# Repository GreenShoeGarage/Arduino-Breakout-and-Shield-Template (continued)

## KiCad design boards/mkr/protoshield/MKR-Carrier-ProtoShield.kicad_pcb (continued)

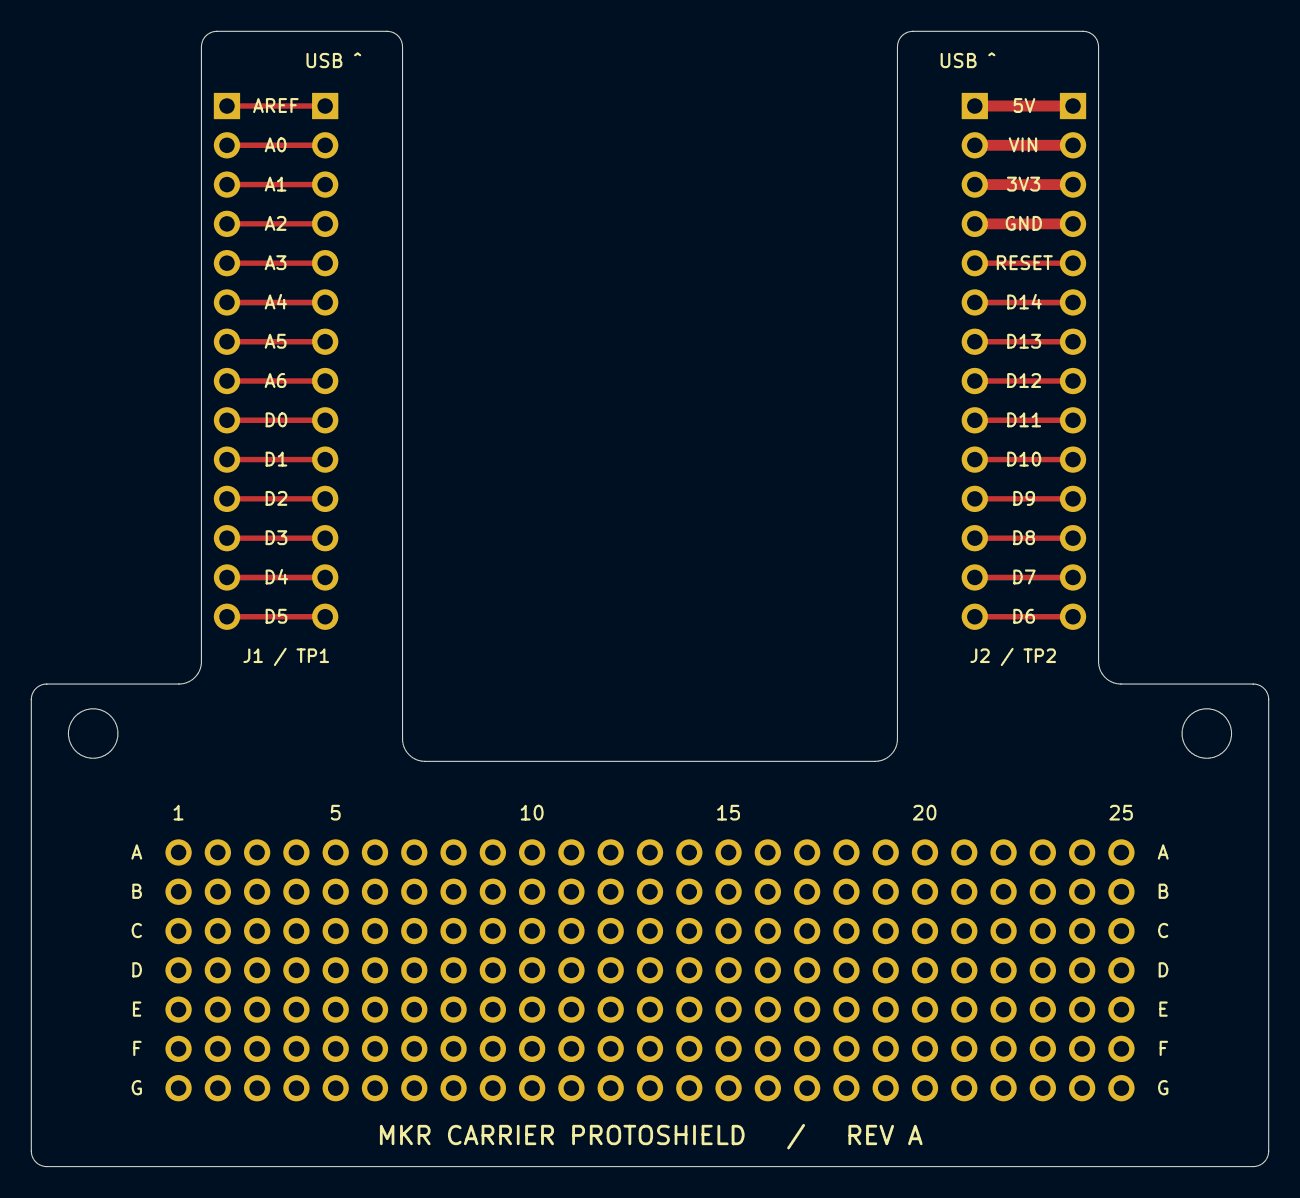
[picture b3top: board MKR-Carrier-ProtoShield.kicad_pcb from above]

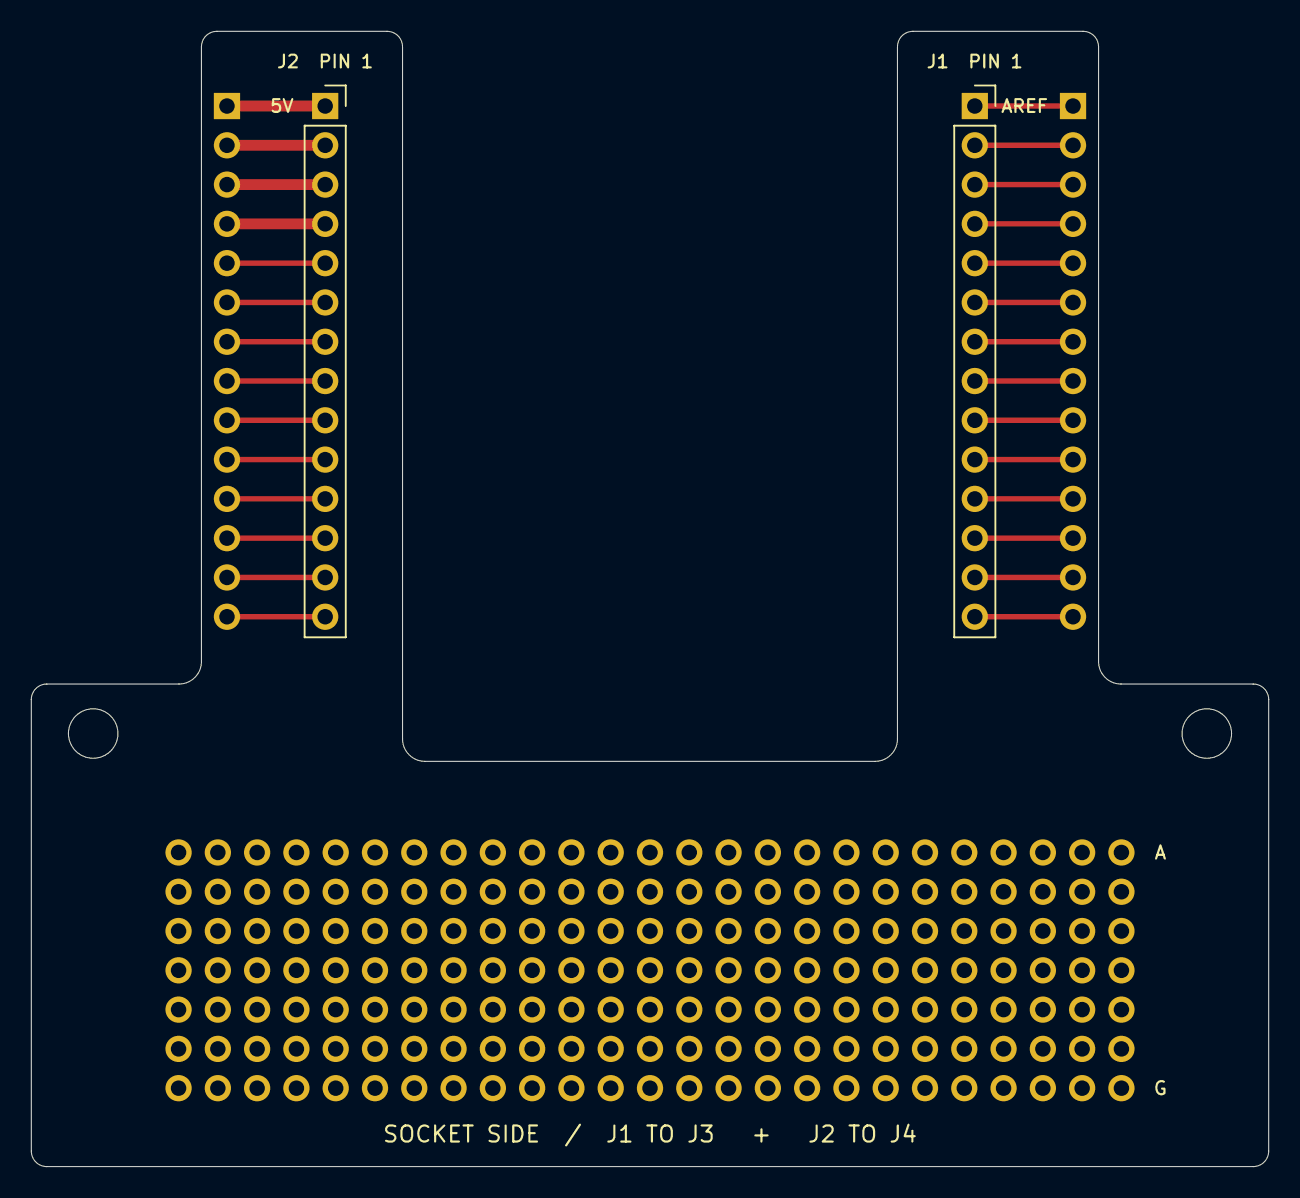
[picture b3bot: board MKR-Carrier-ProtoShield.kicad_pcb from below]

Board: 2 copper layers, 80.0 x 73.4 mm, 13 parts (2 on the bottom side), 28 nets.

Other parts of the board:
H1, H2: M3 clearance; MountingHole_3.2mm_M3

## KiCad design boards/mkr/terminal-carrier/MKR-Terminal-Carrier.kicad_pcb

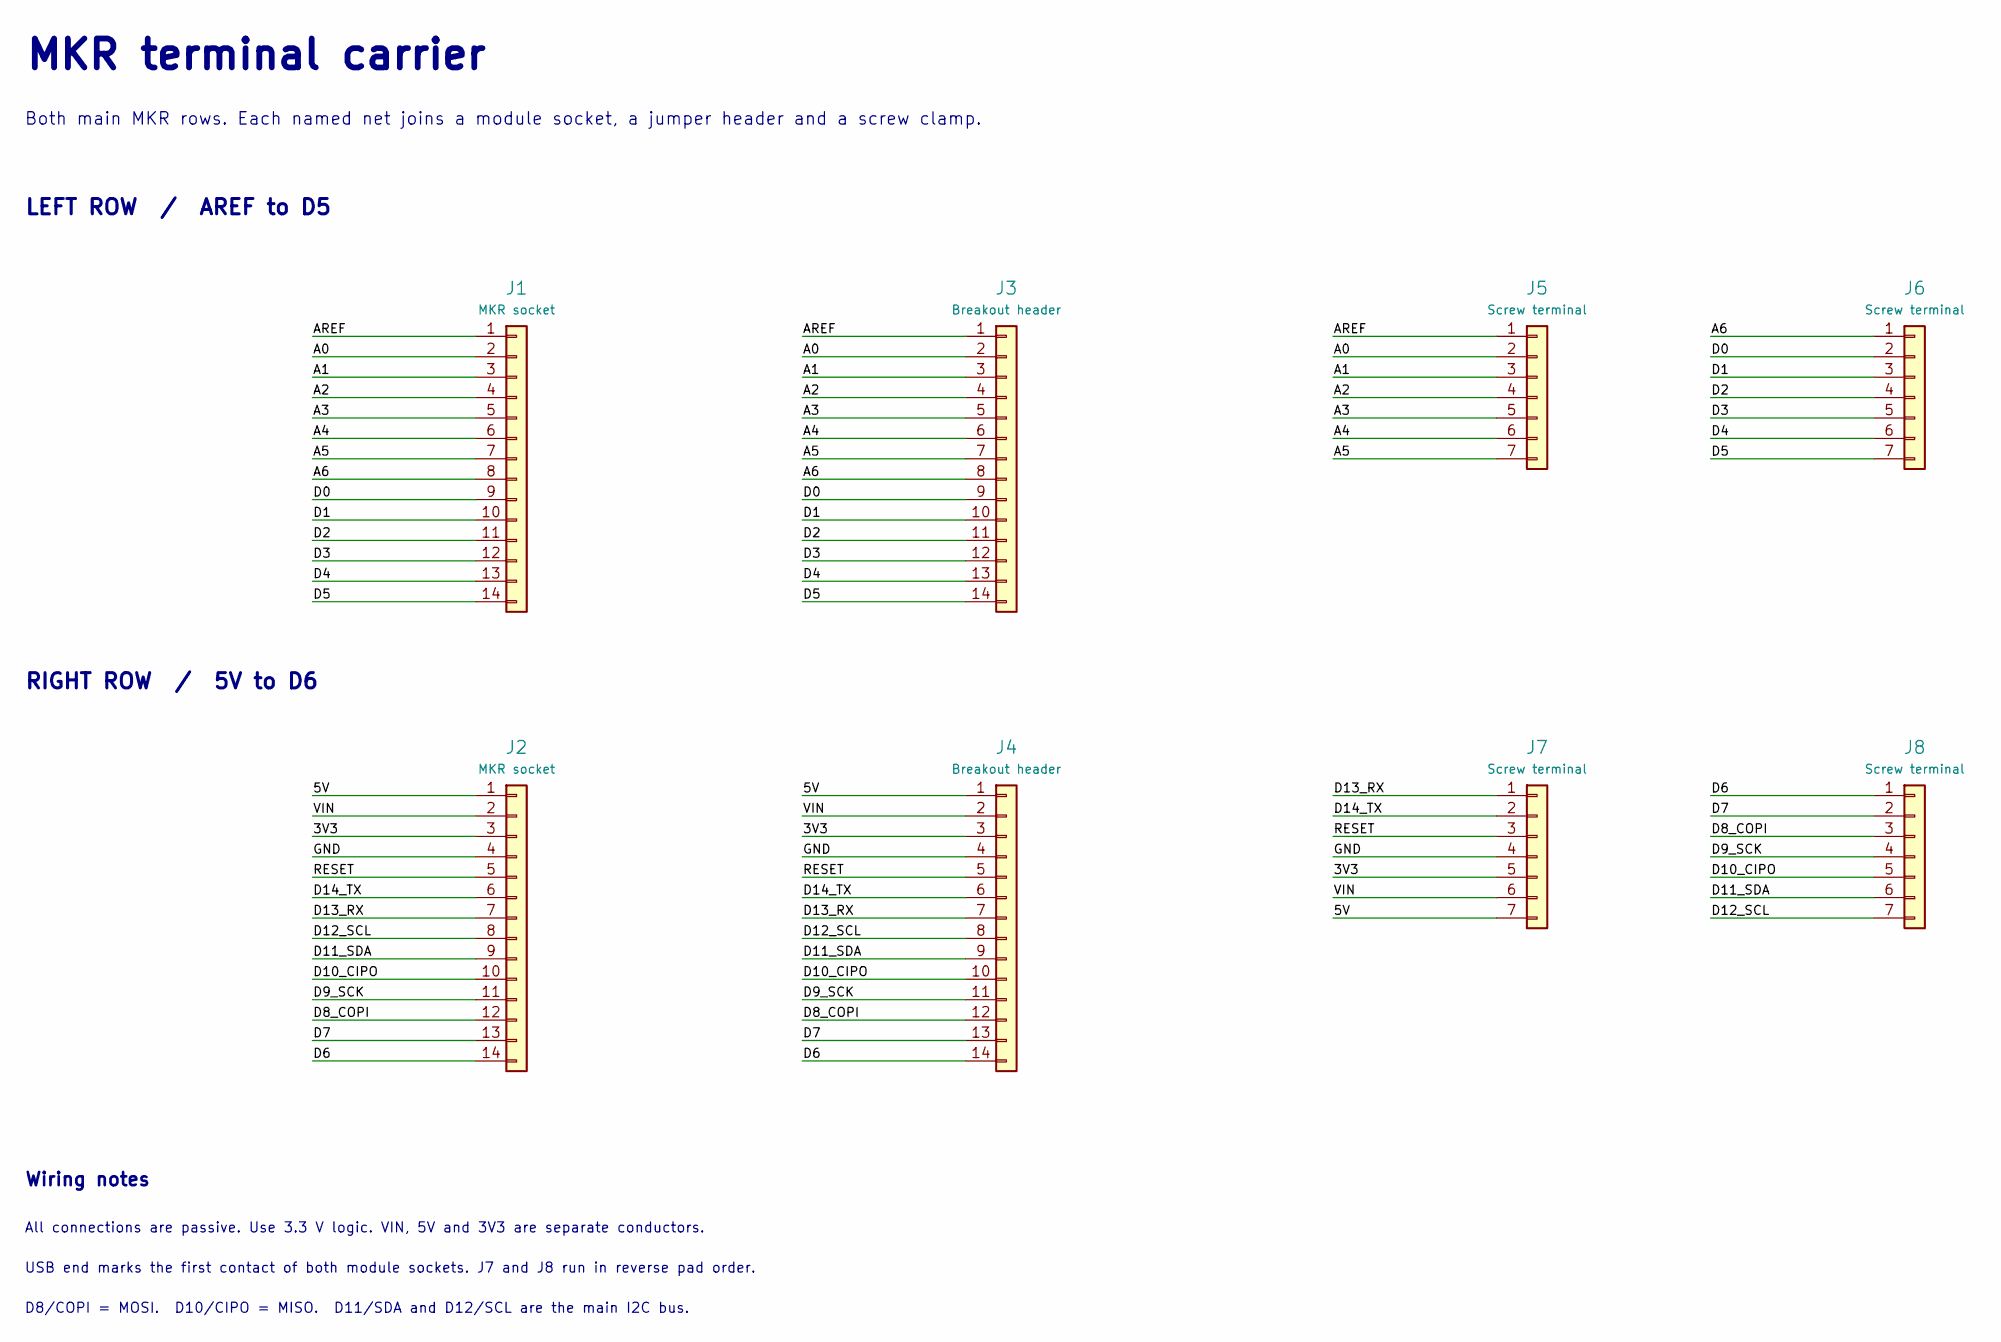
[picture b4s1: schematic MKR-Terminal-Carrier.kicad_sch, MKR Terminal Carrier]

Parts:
J1, J2: MKR socket; PinSocket_1x14_P2.54mm_Vertical; MPN SSW-114-01-G-S
J3, J4: Breakout header; PinHeader_1x14_P2.54mm_Vertical; MPN TSW-114-07-G-S
J5, J6, J7, J8: Screw terminal; TerminalBlock_Phoenix_MPT-0,5-7-2.54_1x07_P2.54mm_Horizontal; MPN 1725708

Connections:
/3V3: J2.3, J4.3, J7.5
/5V: J2.1, J4.1, J7.7
/A0: J1.2, J3.2, J5.2
/A1: J1.3, J3.3, J5.3
/A2: J1.4, J3.4, J5.4
/A3: J1.5, J3.5, J5.5
/A4: J1.6, J3.6, J5.6
/A5: J1.7, J3.7, J5.7
/A6: J1.8, J3.8, J6.1
/AREF: J1.1, J3.1, J5.1
/D0: J1.9, J3.9, J6.2
/D1: J1.10, J3.10, J6.3
/D2: J1.11, J3.11, J6.4
/D3: J1.12, J3.12, J6.5
/D4: J1.13, J3.13, J6.6
/D5: J1.14, J3.14, J6.7
/D6: J2.14, J4.14, J8.1
/D7: J2.13, J4.13, J8.2
/D8_COPI: J2.12, J4.12, J8.3
/D9_SCK: J2.11, J4.11, J8.4
/D10_CIPO: J2.10, J4.10, J8.5
/D11_SDA: J2.9, J4.9, J8.6
/D12_SCL: J2.8, J4.8, J8.7
/D13_RX: J2.7, J4.7, J7.1
/D14_TX: J2.6, J4.6, J7.2
/GND: J2.4, J4.4, J7.4
/RESET: J2.5, J4.5, J7.3
/VIN: J2.2, J4.2, J7.6

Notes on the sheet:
MKR terminal carrier
Both main MKR rows. Each named net joins a module socket, a jumper header and a screw clamp.
LEFT ROW / AREF to D5
RIGHT ROW / 5V to D6
Wiring notes
All connections are passive. Use 3.3 V logic. VIN, 5V and 3V3 are separate conductors.
USB end marks the first contact of both module sockets. J7 and J8 run in reverse pad order.
D8/COPI = MOSI. D10/CIPO = MISO. D11/SDA and D12/SCL are the main I2C bus.

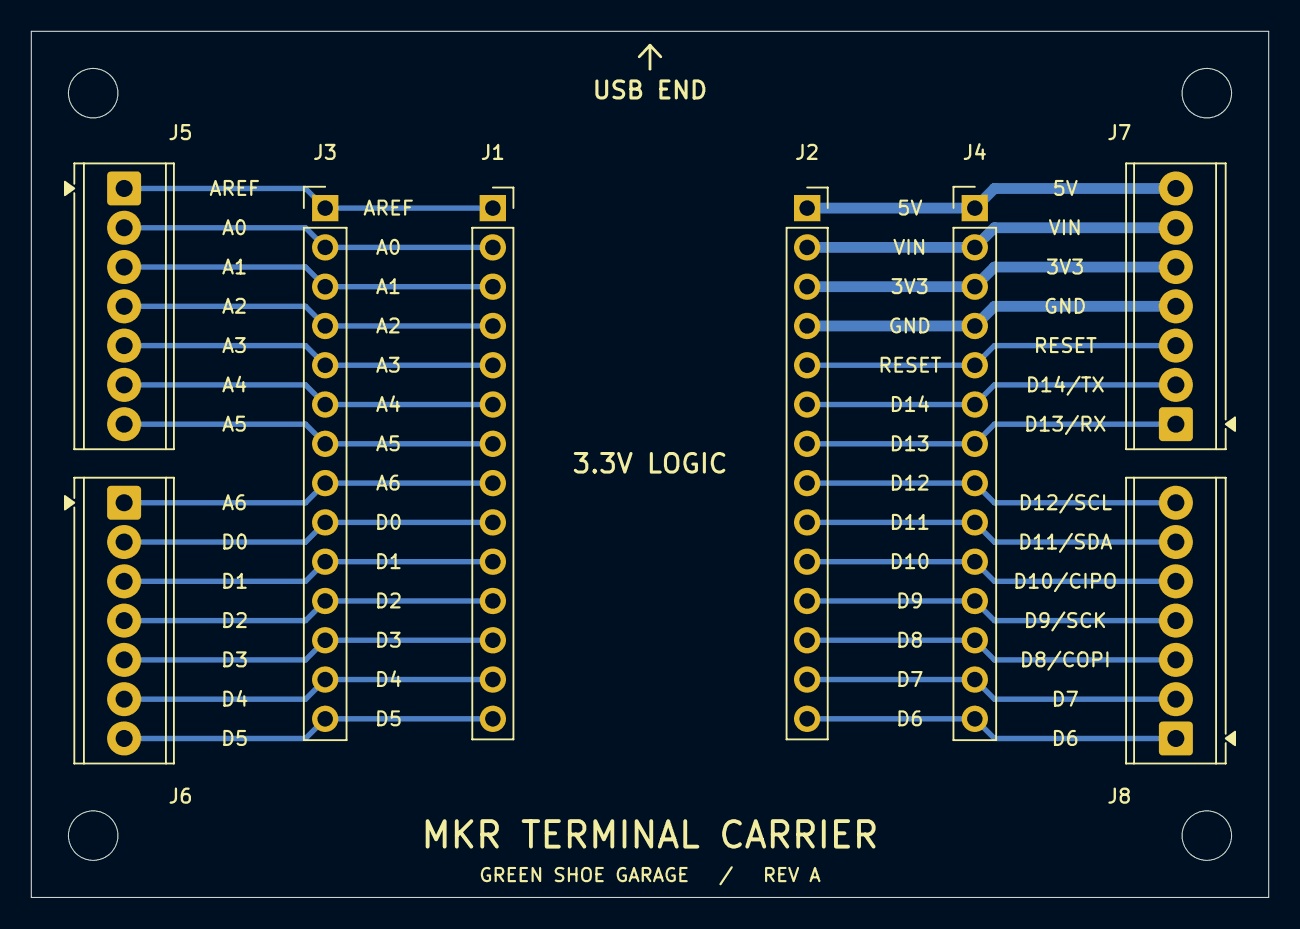
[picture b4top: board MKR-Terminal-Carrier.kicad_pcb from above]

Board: 2 copper layers, 80.0 x 56.0 mm, 12 parts (0 on the bottom side), 28 nets.

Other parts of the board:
H1, H2, H3, H4: M3 clearance; MountingHole_3.2mm_M3

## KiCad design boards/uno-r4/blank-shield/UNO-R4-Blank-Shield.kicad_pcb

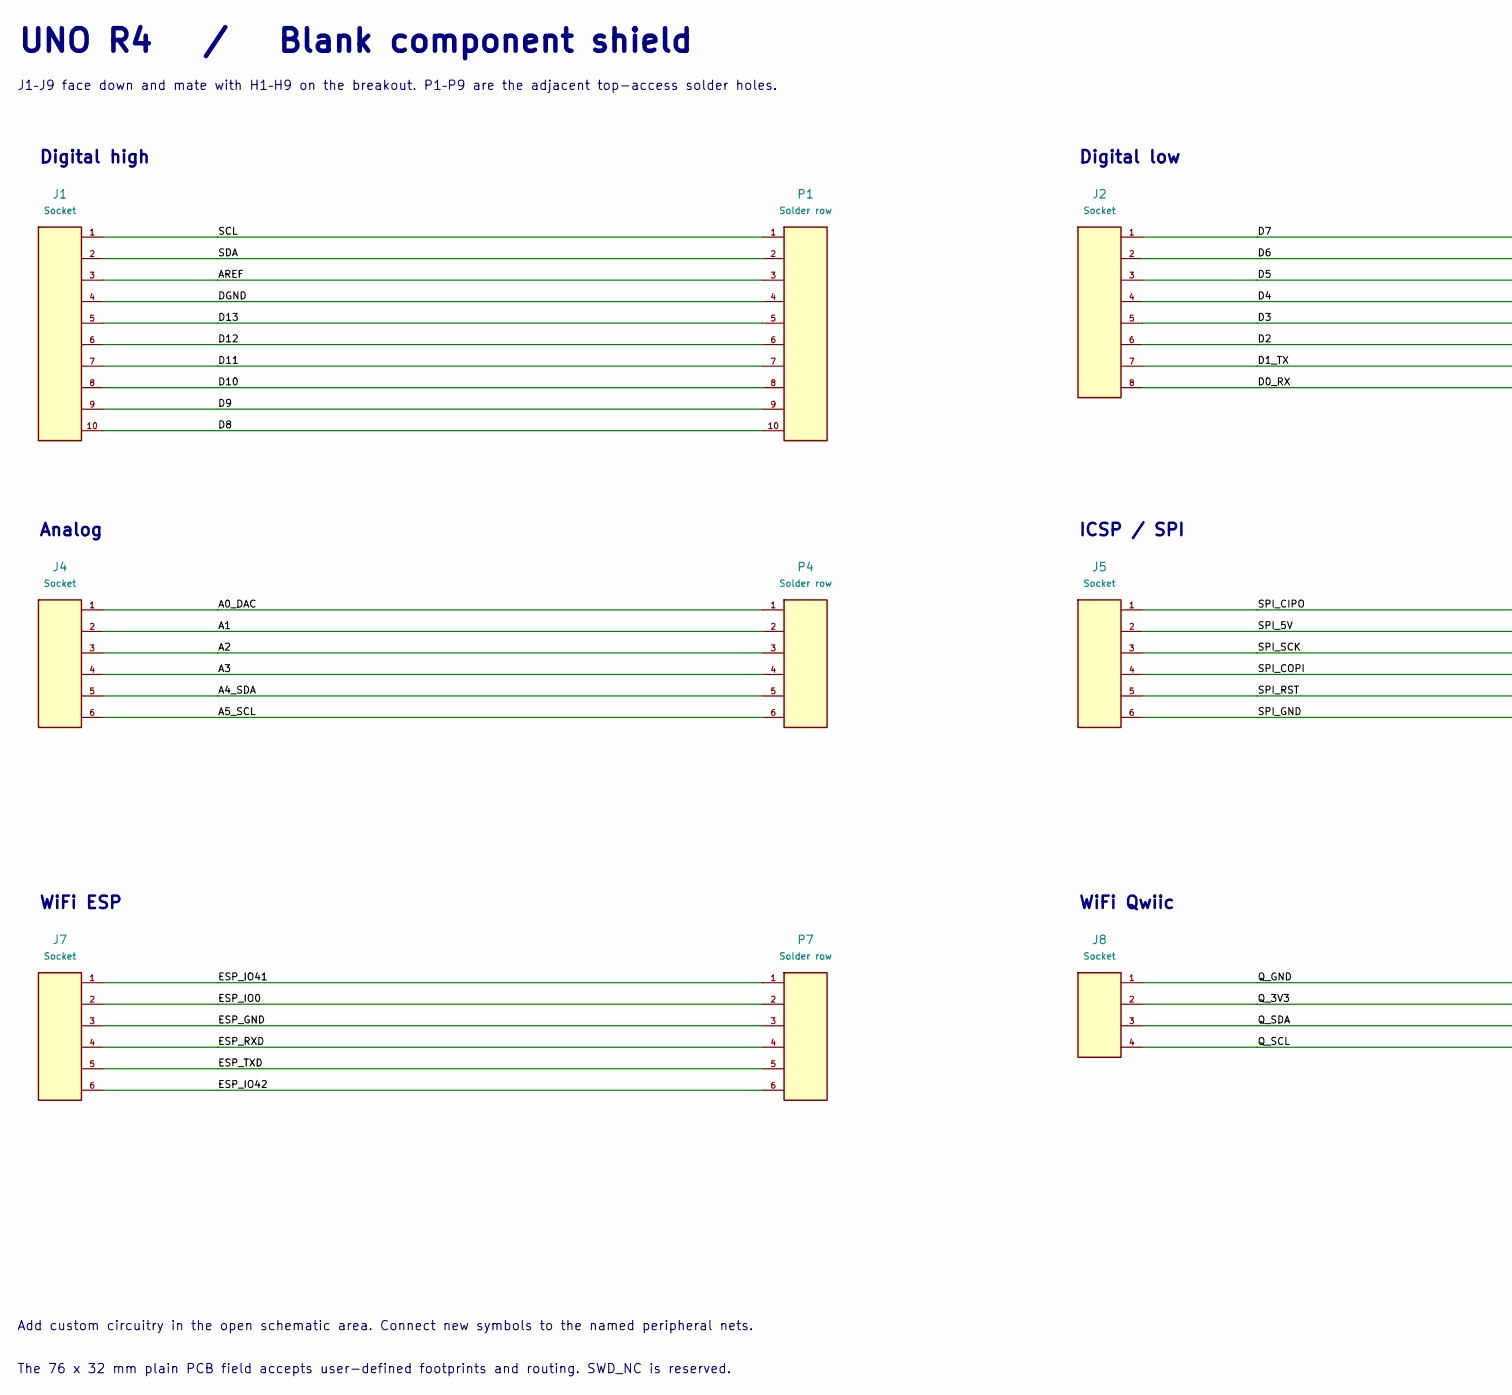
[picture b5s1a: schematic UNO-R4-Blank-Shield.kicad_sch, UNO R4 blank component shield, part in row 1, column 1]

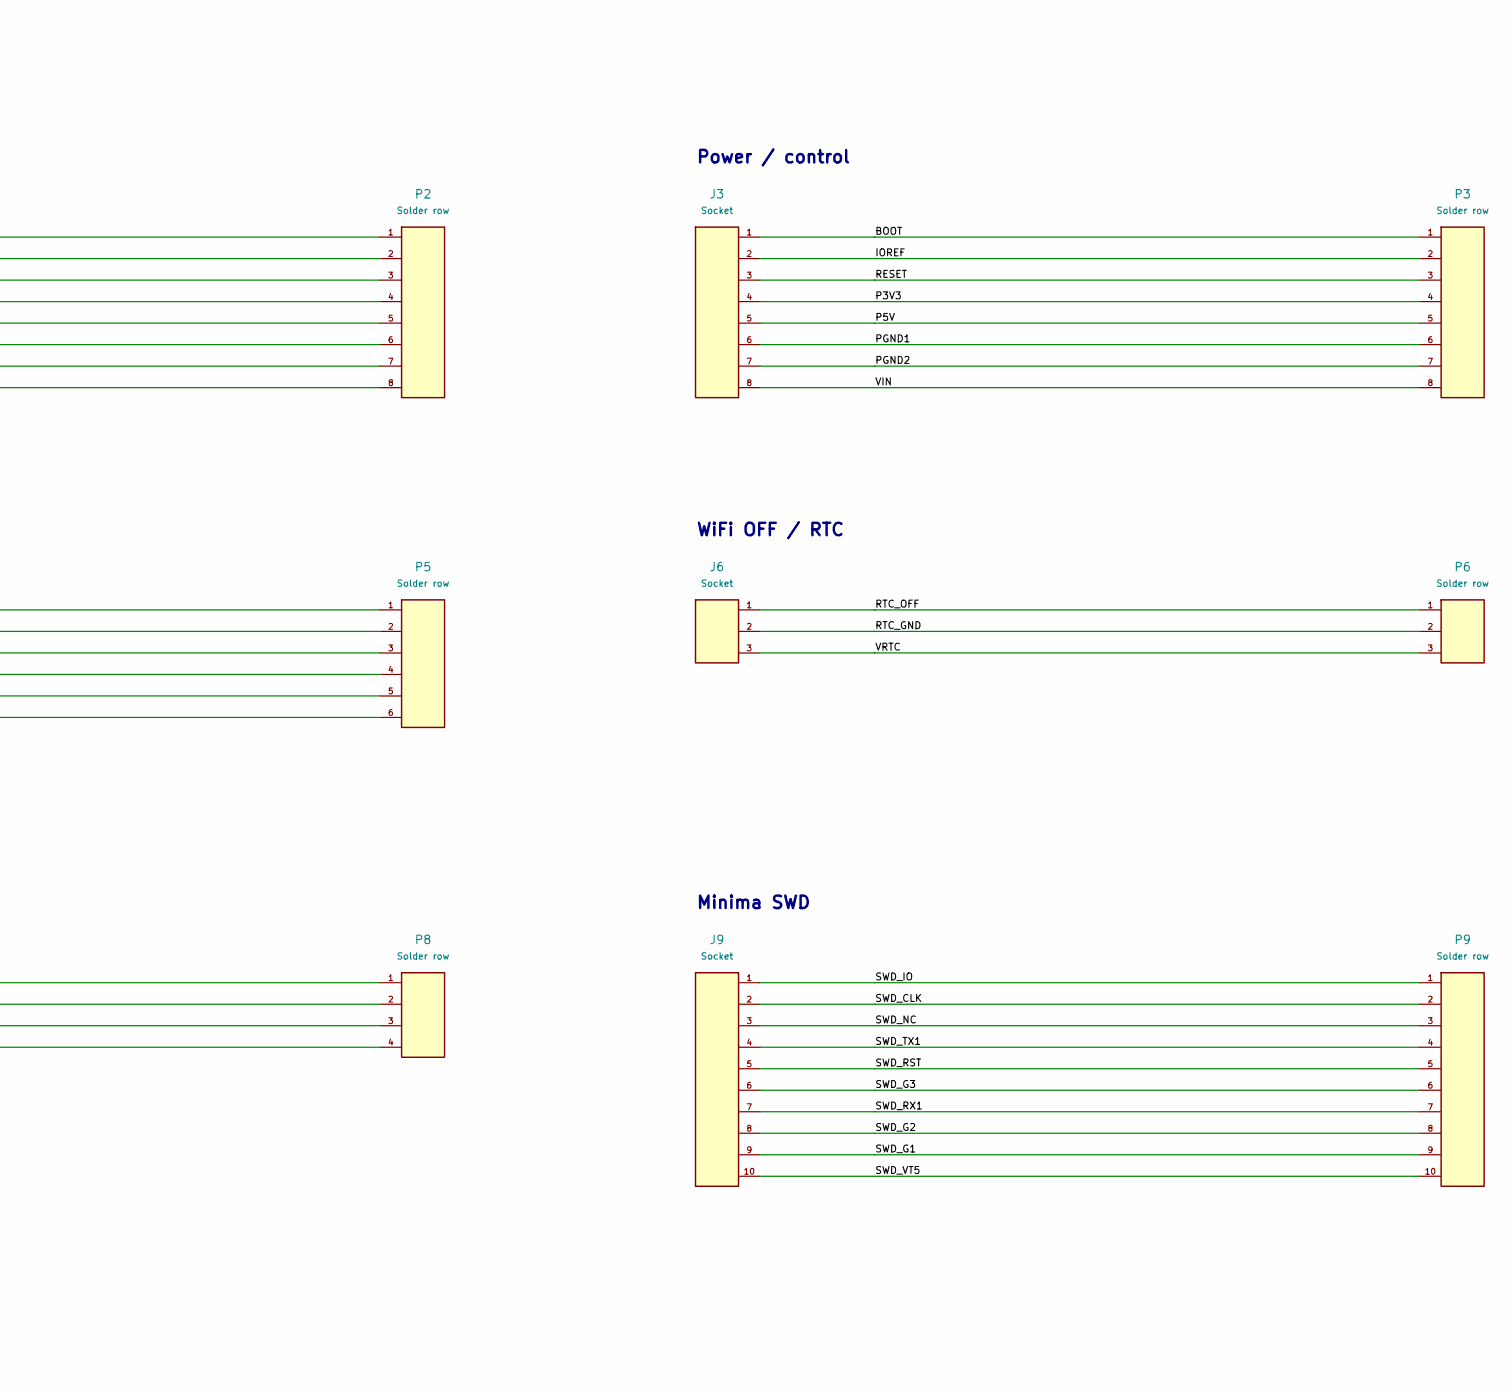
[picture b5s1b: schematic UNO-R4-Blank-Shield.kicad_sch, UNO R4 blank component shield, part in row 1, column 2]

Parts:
J1, J9: Socket; Samtec_SSW-110-21-G-S; MPN SSW-110-21-G-S
J2, J3: Socket; Samtec_SSW-108-21-G-S; MPN SSW-108-21-G-S
J4, J5, J7: Socket; Samtec_SSW-106-21-G-S; MPN SSW-106-21-G-S
J6: Socket; Samtec_SSW-103-21-G-S; MPN SSW-103-21-G-S
J8: Socket; Samtec_SSW-104-21-G-S; MPN SSW-104-21-G-S
P1, P9: Solder row; Solder_10
P2, P3: Solder row; Solder_08
P4, P5, P7: Solder row; Solder_06
P6: Solder row; Solder_03
P8: Solder row; Solder_04

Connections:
/A0_DAC: J4.1, P4.1
/A1: J4.2, P4.2
/A2: J4.3, P4.3
/A3: J4.4, P4.4
/A4_SDA: J4.5, P4.5
/A5_SCL: J4.6, P4.6
/AREF: J1.3, P1.3
/BOOT: J3.1, P3.1
/D0_RX: J2.8, P2.8
/D1_TX: J2.7, P2.7
/D2: J2.6, P2.6
/D3: J2.5, P2.5
/D4: J2.4, P2.4
/D5: J2.3, P2.3
/D6: J2.2, P2.2
/D7: J2.1, P2.1
/D8: J1.10, P1.10
/D9: J1.9, P1.9
/D10: J1.8, P1.8
/D11: J1.7, P1.7
/D12: J1.6, P1.6
/D13: J1.5, P1.5
/DGND: J1.4, P1.4
/ESP_GND: J7.3, P7.3
/ESP_IO0: J7.2, P7.2
/ESP_IO41: J7.1, P7.1
/ESP_IO42: J7.6, P7.6
/ESP_RXD: J7.4, P7.4
/ESP_TXD: J7.5, P7.5
/IOREF: J3.2, P3.2
/P3V3: J3.4, P3.4
/P5V: J3.5, P3.5
/PGND1: J3.6, P3.6
/PGND2: J3.7, P3.7
/Q_3V3: J8.2, P8.2
/Q_GND: J8.1, P8.1
/Q_SCL: J8.4, P8.4
/Q_SDA: J8.3, P8.3
/RESET: J3.3, P3.3
/RTC_GND: J6.2, P6.2
/RTC_OFF: J6.1, P6.1
/SCL: J1.1, P1.1
/SDA: J1.2, P1.2
/SPI_5V: J5.2, P5.2
/SPI_CIPO: J5.1, P5.1
/SPI_COPI: J5.4, P5.4
/SPI_GND: J5.6, P5.6
/SPI_RST: J5.5, P5.5
/SPI_SCK: J5.3, P5.3
/SWD_CLK: J9.2, P9.2
/SWD_G1: J9.9, P9.9
/SWD_G2: J9.8, P9.8
/SWD_G3: J9.6, P9.6
/SWD_IO: J9.1, P9.1
/SWD_NC: J9.3, P9.3
/SWD_RST: J9.5, P9.5
/SWD_RX1: J9.7, P9.7
/SWD_TX1: J9.4, P9.4
/SWD_VT5: J9.10, P9.10
/VIN: J3.8, P3.8
/VRTC: J6.3, P6.3

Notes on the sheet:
UNO R4 / Blank component shield
J1–J9 face down and mate with H1–H9 on the breakout. P1–P9 are the adjacent top-access solder holes.
Digital high
Digital low
Power / control
Analog
ICSP / SPI
WiFi OFF / RTC
WiFi ESP
WiFi Qwiic
Minima SWD
Add custom circuitry in the open schematic area. Connect new symbols to the named peripheral nets.
The 76 x 32 mm plain PCB field accepts user-defined footprints and routing. SWD_NC is reserved.

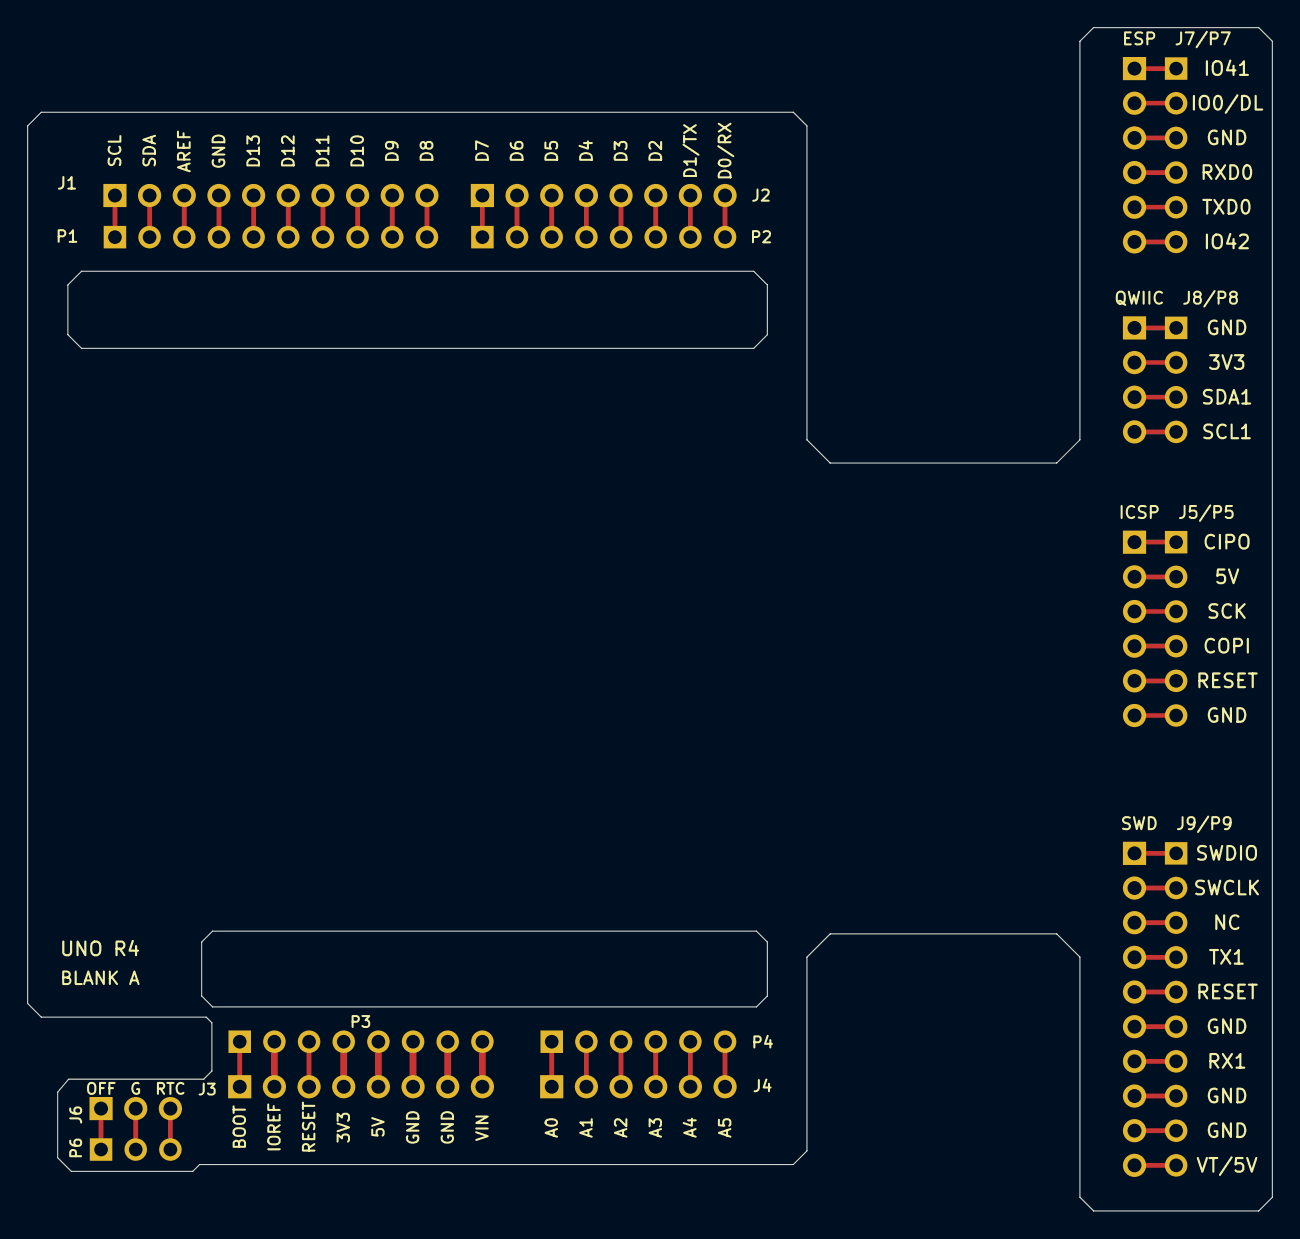
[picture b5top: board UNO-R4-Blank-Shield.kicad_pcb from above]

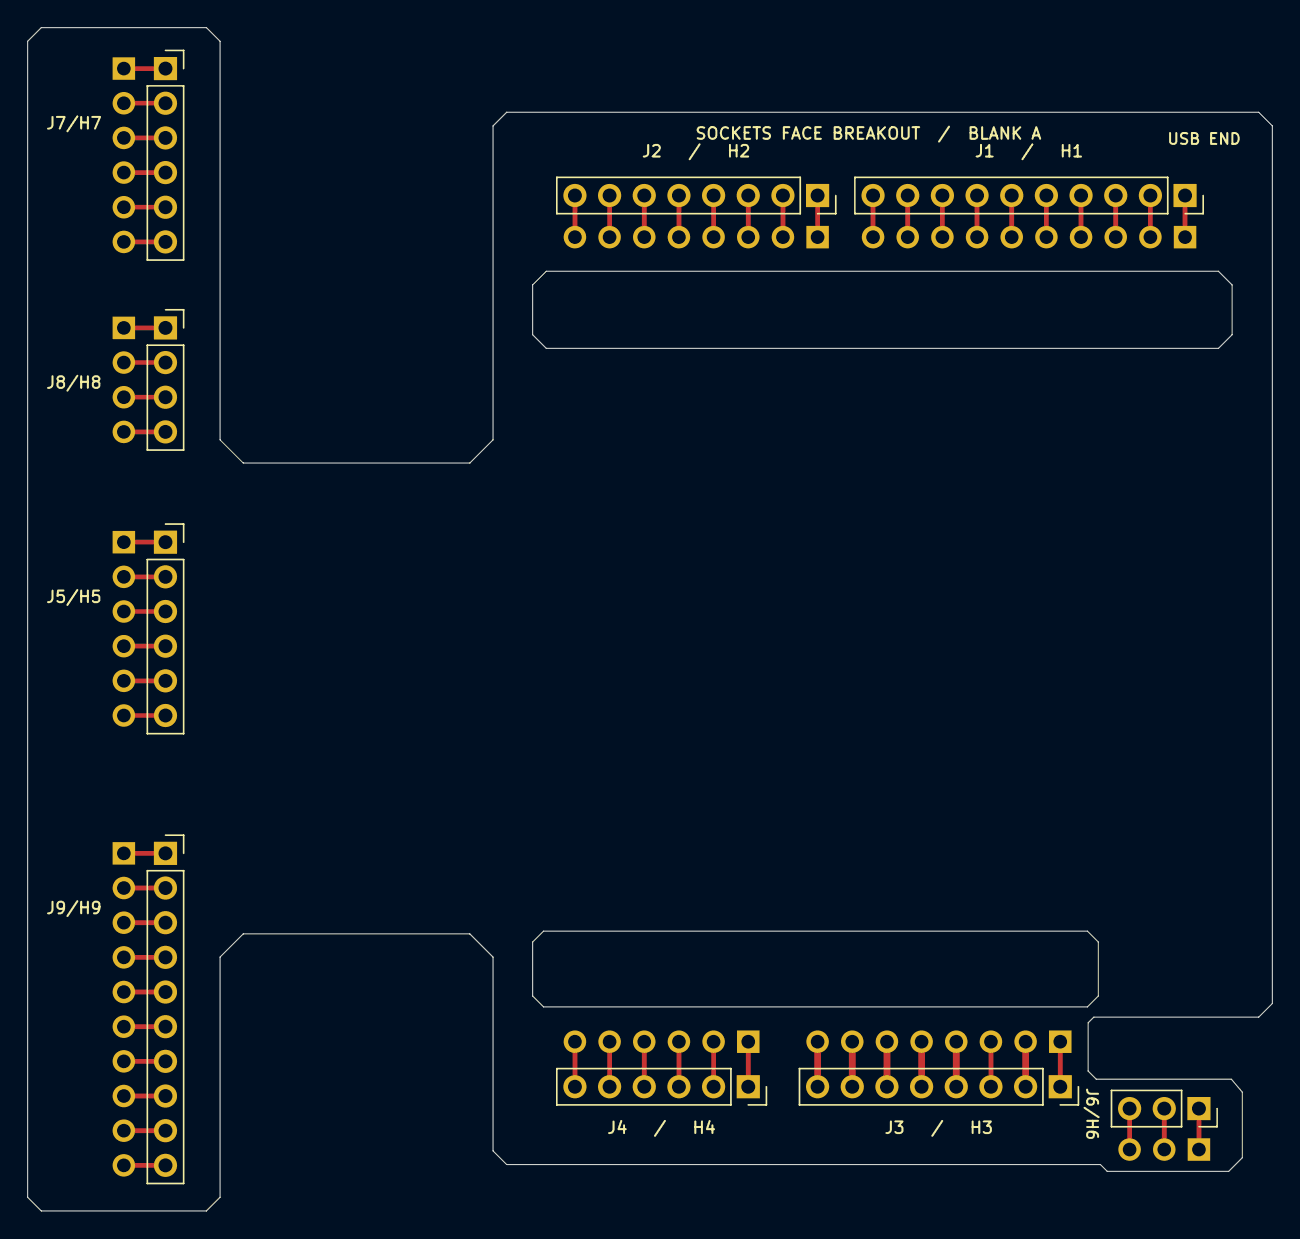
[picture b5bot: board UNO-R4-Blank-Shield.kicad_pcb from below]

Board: 2 copper layers, 91.2 x 86.7 mm, 18 parts (9 on the bottom side), 61 nets.
